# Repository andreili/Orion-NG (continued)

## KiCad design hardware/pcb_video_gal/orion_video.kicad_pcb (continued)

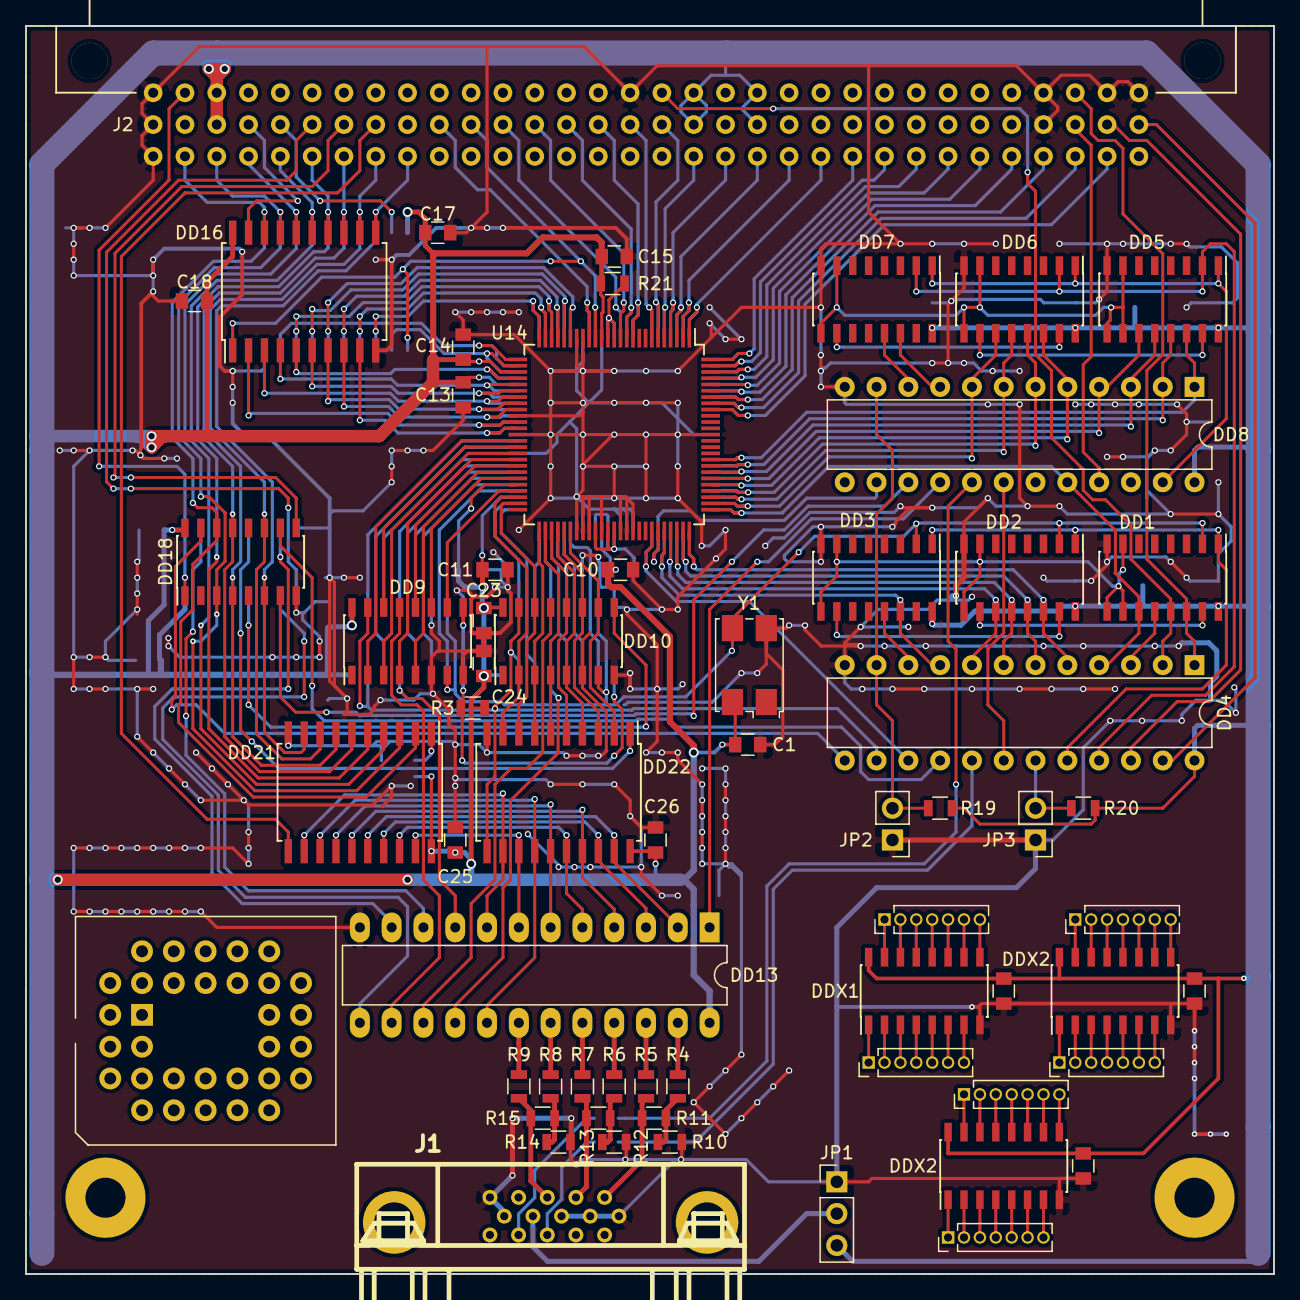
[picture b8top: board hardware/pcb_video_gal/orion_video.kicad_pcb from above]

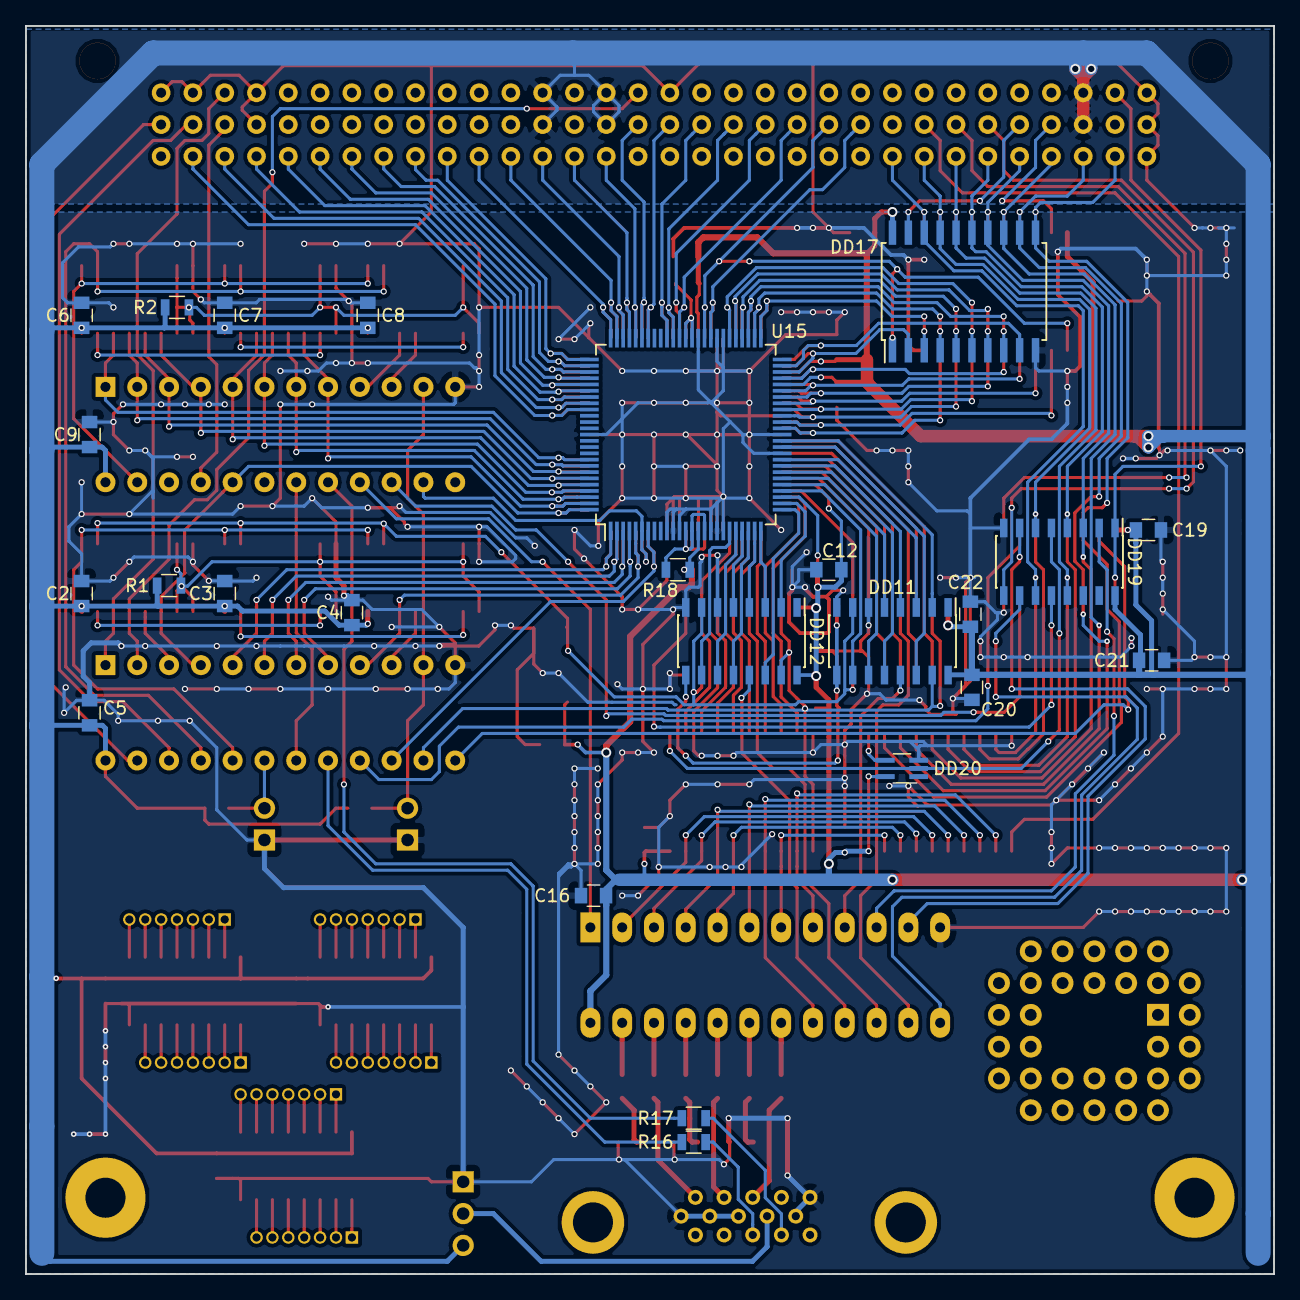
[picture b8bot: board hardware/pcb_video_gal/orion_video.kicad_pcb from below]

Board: 2 copper layers, 99.7 x 99.7 mm, 87 parts (25 on the bottom side), 181 nets.

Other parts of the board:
C27#2, C27#3: 100n; C_0805
DDX1, DDX2, DDX2#2: KP11; SOIC-16_3.9x9.9mm_Pitch1.27mm
J3#2, J3#3, J4#2, J4#3: RES1; Pin_Header_Straight_1x07_Pitch1.27mm

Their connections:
GND: C27#2.2, C27#3.2, DDX1.8, DDX2.8, DDX2#2.8; also elsewhere on the board
R1: DDX1.1, DDX2.1, DDX2#2.1, J3#2.1, J3#3.1; also elsewhere on the board
R2: DDX1.2, DDX2.2, DDX2#2.2, J3#2.2, J3#3.2; also elsewhere on the board
R3: DDX1.3, DDX2.3, DDX2#2.3, J3#2.3, J3#3.3; also elsewhere on the board
R4: DDX1.4, DDX2.4, DDX2#2.4, J3#2.4, J3#3.4; also elsewhere on the board
R5: DDX1.5, DDX2.5, DDX2#2.5, J3#2.5, J3#3.5; also elsewhere on the board
R6: DDX1.6, DDX2.6, DDX2#2.6, J3#2.6, J3#3.6; also elsewhere on the board
R7: DDX1.7, DDX2.7, DDX2#2.7, J3#2.7, J3#3.7; also elsewhere on the board
R9: DDX1.9, DDX2.9, DDX2#2.9, J4#2.7, J4#3.7; also elsewhere on the board
R10: DDX1.10, DDX2.10, DDX2#2.10, J4#2.6, J4#3.6; also elsewhere on the board
R11: DDX1.11, DDX2.11, DDX2#2.11, J4#2.5, J4#3.5; also elsewhere on the board
R12: DDX1.12, DDX2.12, DDX2#2.12, J4#2.4, J4#3.4; also elsewhere on the board
R13: DDX1.13, DDX2.13, DDX2#2.13, J4#2.3, J4#3.3; also elsewhere on the board
R14: DDX1.14, DDX2.14, DDX2#2.14, J4#2.2, J4#3.2; also elsewhere on the board
R15: DDX1.15, DDX2.15, DDX2#2.15, J4#2.1, J4#3.1; also elsewhere on the board
VCC: C27#2.1, C27#3.1, DDX1.16, DDX2.16, DDX2#2.16; also elsewhere on the board

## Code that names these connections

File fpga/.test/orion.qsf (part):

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set_location_assignment PIN_AJ24 -to ZD[2]
set_location_assignment PIN_AK24 -to ZD[1]
set_location_assignment PIN_AG23 -to ZD[0]
set_location_assignment PIN_AK23 -to ZRES
set_location_assignment PIN_AH23 -to ZCLK
set_location_assignment PIN_AK22 -to ZRFSH
set_location_assignment PIN_AJ22 -to ZINT
set_location_assignment PIN_AH22 -to ZMREQ
set_location_assignment PIN_AF24 -to ZIORQ
set_location_assignment PIN_AF23 -to ZWR
set_location_assignment PIN_AD21 -to ZRD
set_location_assignment PIN_AG22 -to ZM1
set_instance_assignment -name IO_STANDARD "3.3-V LVCMOS" -to ZA[1]
set_instance_assignment -name IO_STANDARD "3.3-V LVCMOS" -to ZA[0]
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
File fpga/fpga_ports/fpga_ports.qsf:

# -------------------------------------------------------------------------- #
#
# Copyright (C) 1991-2013 Altera Corporation
# Your use of Altera Corporation's design tools, logic functions 
# and other software and tools, and its AMPP partner logic 
# functions, and any output files from any of the foregoing 
# (including device programming or simulation files), and any 
# associated documentation or information are expressly subject 
# to the terms and conditions of the Altera Program License 
# Subscription Agreement, Altera MegaCore Function License 
# Agreement, or other applicable license agreement, including, 
# without limitation, that your use is for the sole purpose of 
# programming logic devices manufactured by Altera and sold by 
# Altera or its authorized distributors.  Please refer to the 
# applicable agreement for further details.
#
# -------------------------------------------------------------------------- #
#
# Quartus II 64-Bit
# Version 13.0.1 Build 232 06/12/2013 Service Pack 1 SJ Web Edition
# Date created = 19:53:07  June 26, 2018
#
# -------------------------------------------------------------------------- #
#
# Notes:
#
# 1) The default values for assignments are stored in the file:
#		fpga_vmem_assignment_defaults.qdf
#    If this file doesn't exist, see file:
#		assignment_defaults.qdf
#
# 2) Altera recommends that you do not modify this file. This
#    file is updated automatically by the Quartus II software
#    and any changes you make may be lost or overwritten.
#
# -------------------------------------------------------------------------- #


set_global_assignment -name FAMILY MAX7000S
set_global_assignment -name DEVICE "EPM7128STC100-7"
set_global_assignment -name TOP_LEVEL_ENTITY cpu_ports
set_global_assignment -name ORIGINAL_QUARTUS_VERSION "13.0 SP1"
set_global_assignment -name PROJECT_CREATION_TIME_DATE "19:53:07  JUNE 26, 2018"
set_global_assignment -name LAST_QUARTUS_VERSION "13.0 SP1"
set_global_assignment -name PROJECT_OUTPUT_DIRECTORY output_files
set_global_assignment -name DEVICE_FILTER_PACKAGE TQFP
set_global_assignment -name DEVICE_FILTER_PIN_COUNT 100
set_global_assignment -name DEVICE_FILTER_SPEED_GRADE 7
set_global_assignment -name ERROR_CHECK_FREQUENCY_DIVISOR "-1"

set_global_assignment -name MAX7000_DEVICE_IO_STANDARD TTL
set_location_assignment PIN_4 -to TDI
set_location_assignment PIN_15 -to TMS
set_location_assignment PIN_62 -to TCK
set_location_assignment PIN_73 -to TDO
set_location_assignment PIN_87 -to clk
set_global_assignment -name MAX7000_OPTIMIZATION_TECHNIQUE AREA
set_global_assignment -name SYNTH_TIMING_DRIVEN_SYNTHESIS OFF
set_global_assignment -name OPTIMIZE_HOLD_TIMING OFF
set_global_assignment -name OPTIMIZE_MULTI_CORNER_TIMING ON
set_global_assignment -name FITTER_EFFORT "STANDARD FIT"
set_location_assignment PIN_54 -to addr[0]
set_location_assignment PIN_24 -to addr[1]
set_location_assignment PIN_20 -to addr[2]
set_location_assignment PIN_97 -to addr[3]
set_location_assignment PIN_32 -to addr[4]
set_location_assignment PIN_28 -to addr[5]
set_location_assignment PIN_65 -to addr[6]
set_location_assignment PIN_98 -to addr[15]
set_location_assignment PIN_27 -to addr[7]
set_location_assignment PIN_85 -to addr[14]
set_location_assignment PIN_81 -to addr[8]
set_location_assignment PIN_94 -to addr[13]
set_location_assignment PIN_68 -to addr[9]
set_location_assignment PIN_30 -to addr[12]
set_location_assignment PIN_69 -to addr[10]
set_location_assignment PIN_56 -to addr[11]
set_global_assignment -name PRE_MAPPING_RESYNTHESIS OFF
set_global_assignment -name MAX7000_FANIN_PER_CELL 80
set_global_assignment -name IGNORE_CARRY_BUFFERS OFF
set_global_assignment -name IGNORE_CASCADE_BUFFERS OFF
set_global_assignment -name IGNORE_GLOBAL_BUFFERS OFF
set_global_assignment -name IGNORE_ROW_GLOBAL_BUFFERS OFF
set_global_assignment -name MAX7000_IGNORE_LCELL_BUFFERS AUTO
set_global_assignment -name MAX7000_IGNORE_SOFT_BUFFERS OFF
set_global_assignment -name AUTO_RESOURCE_SHARING OFF
set_global_assignment -name ECO_REGENERATE_REPORT OFF
set_global_assignment -name OPTIMIZE_IOC_REGISTER_PLACEMENT_FOR_TIMING "PACK ALL IO REGISTERS"
set_global_assignment -name FORCE_FITTER_TO_AVOID_PERIPHERY_PLACEMENT_WARNINGS OFF
set_global_assignment -name ALM_REGISTER_PACKING_EFFORT HIGH
set_global_assignment -name STATE_MACHINE_PROCESSING "MINIMAL BITS"
set_global_assignment -name VHDL_INPUT_VERSION VHDL_2008
set_global_assignment -name VHDL_SHOW_LMF_MAPPING_MESSAGES OFF
set_global_assignment -name AUTO_PARALLEL_EXPANDERS OFF

set_global_assignment -name AUTO_LCELL_INSERTION ON
set_global_assignment -name REMOVE_DUPLICATE_REGISTERS OFF
set_global_assignment -name SYNTHESIS_SEED 47
set_global_assignment -name AUTO_TURBO_BIT ON
set_global_assignment -name ECO_OPTIMIZE_TIMING ON
set_instance_assignment -name GLOBAL_SIGNAL "GLOBAL CLOCK" -to clk
set_location_assignment PIN_67 -to data[4]
set_location_assignment PIN_80 -to data[3]
set_location_assignment PIN_55 -to data[5]
set_global_assignment -name ASSIGNMENT_GROUP_MEMBER config -section_id config_gr
set_location_assignment PIN_22 -to rfshn
set_location_assignment PIN_92 -to m1n
set_location_assignment PIN_89 -to resetn
set_location_assignment PIN_58 -to waitn
set_location_assignment PIN_90 -to wrn
set_location_assignment PIN_33 -to rdn
set_location_assignment PIN_61 -to data[6]
set_location_assignment PIN_8 -to data[2]
set_location_assignment PIN_64 -to data[7]
set_location_assignment PIN_25 -to data[0]
set_location_assignment PIN_29 -to data[1]
set_location_assignment PIN_10 -to ram_vm_oe0
set_location_assignment PIN_9 -to ram_vm_oe1
set_location_assignment PIN_96 -to snd
set_location_assignment PIN_50 -to rom3_sel
set_location_assignment PIN_49 -to rom2_sel
set_location_assignment PIN_44 -to rom2_addr[13]
set_location_assignment PIN_45 -to rom2_addr[14]
set_location_assignment PIN_47 -to rom2_addr[15]
set_location_assignment PIN_48 -to rom2_addr[16]
set_location_assignment PIN_46 -to rom2_addr[17]
set_location_assignment PIN_52 -to rom2_addr[18]
set_location_assignment PIN_42 -to rom1_sel
set_location_assignment PIN_41 -to ram_wrn
set_location_assignment PIN_40 -to ram_rdn
set_location_assignment PIN_1 -to ram_cen_v
set_location_assignment PIN_14 -to ram_cen[0]
set_location_assignment PIN_16 -to ram_cen[1]
set_location_assignment PIN_17 -to ram_cen[2]
set_location_assignment PIN_19 -to ram_cen[3]
set_location_assignment PIN_99 -to pFC
set_location_assignment PIN_63 -to pFB
set_location_assignment PIN_100 -to pFA
set_location_assignment PIN_36 -to pF8
set_location_assignment PIN_93 -to mreqn
set_location_assignment PIN_23 -to MA[14]
set_location_assignment PIN_2 -to MA[15]
set_location_assignment PIN_7 -to MA[16]
set_location_assignment PIN_6 -to MA[17]
set_location_assignment PIN_5 -to MA[18]
set_location_assignment PIN_53 -to irq0n
set_location_assignment PIN_88 -to iorqn
set_location_assignment PIN_37 -to int50
set_location_assignment PIN_70 -to config[0]
set_location_assignment PIN_71 -to config[1]
set_location_assignment PIN_72 -to config[2]
set_location_assignment PIN_75 -to config[3]
set_location_assignment PIN_76 -to config[4]
set_location_assignment PIN_77 -to config[5]
set_location_assignment PIN_78 -to config[6]
set_location_assignment PIN_79 -to config[7]
set_location_assignment PIN_57 -to blion
set_location_assignment PIN_21 -to addr_hi[14]
set_location_assignment PIN_35 -to addr_hi[15]
set_location_assignment PIN_84 -to zclk
set_location_assignment PIN_60 -to clk_sel
set_location_assignment PIN_31 -to ram_16bit
set_location_assignment PIN_12 -to ram_buf_oe[0]
set_location_assignment PIN_13 -to ram_buf_oe[1]
set_location_assignment PIN_83 -to res
set_global_assignment -name SDC_FILE fpga_ports.out.sdc
set_global_assignment -name VHDL_FILE rtl/cpu_ports.vhd
set_global_assignment -name SEARCH_PATH rtl/ -tag from_archive

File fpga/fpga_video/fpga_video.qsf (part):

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set_instance_assignment -name IO_STANDARD "3.3-V LVCMOS" -to EXT3[5]
set_instance_assignment -name IO_STANDARD "3.3-V LVCMOS" -to EXT3[6]
set_instance_assignment -name IO_STANDARD "3.3-V LVCMOS" -to EXT3[7]
set_location_assignment PIN_K16 -to EXT1[5]
set_location_assignment PIN_J12 -to EXT1[4]
set_location_assignment PIN_J13 -to EXT1[3]
set_location_assignment PIN_J16 -to EXT1[2]
set_location_assignment PIN_J15 -to EXT1[1]
set_location_assignment PIN_J14 -to EXT1[0]
set_location_assignment PIN_B12 -to EXT0[7]
set_location_assignment PIN_B16 -to EXT0[6]
set_location_assignment PIN_D12 -to EXT0[5]
set_location_assignment PIN_A15 -to EXT0[4]
set_location_assignment PIN_A13 -to EXT0[3]
set_location_assignment PIN_A14 -to EXT0[2]
set_location_assignment PIN_B13 -to EXT0[1]
set_location_assignment PIN_B14 -to EXT0[0]
set_global_assignment -name ENABLE_SIGNALTAP ON
set_global_assignment -name USE_SIGNALTAP_FILE stp1.stp
set_location_assignment PIN_N9 -to EXT2_4
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set_location_assignment PIN_C11 -to IO1_14
set_location_assignment PIN_R11 -to EXT2_2
set_location_assignment PIN_R12 -to EXT2_1
set_location_assignment PIN_P9 -to EXT3[7]
set_location_assignment PIN_R9 -to EXT3[5]
set_location_assignment PIN_N5 -to EXT3[6]
set_location_assignment PIN_R6 -to EXT3[4]
set_location_assignment PIN_P8 -to EXT3[3]
set_location_assignment PIN_R7 -to EXT3[2]
set_instance_assignment -name IO_STANDARD "3.3-V LVCMOS" -to RESET_N
set_location_assignment PIN_P11 -to RESET_N
set_global_assignment -name OPTIMIZATION_MODE "AGGRESSIVE PERFORMANCE"
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
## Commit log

2018-05-07 Оптимизирована логика видеовыхода
2018-05-09 Оптимизация GAL_X - освобождён 1 выход для дальнейшего использования в менеджере памяти.
2018-05-10 Оптимизация прошавки GAL_X - добавлено формирование сигналов арбитража памяти и банков видеопамяти.
2018-05-11 Прошивки GAL обновлены до актуальных версий
2018-05-11 Завершена черновая схема видеомодуля.
2018-05-11 Обновлена схема видеомодуля
2018-05-11 Предварительное размещение элементов
2018-05-12 Исправления по схеме видеомодуля:
    1) Заменён системный разъём на DIN 41612;
    2) ПЗУ знакогенератора заменена на 28C512;
    3) Добавлена коммутация подачи питания на пин 9 разъёма VGA.
2018-05-15 Исправлен системный разъём - выполнен 3-х рядным DIN
2018-05-16 Обновлено расположение компонентов, разъём SYSTEM заменён на 3-х рядный.
2018-07-19 Добавлена реализация основных алгоритмов на CPLD
2018-07-19 Ширина андресной шины увеличена до 21 бита
2018-07-19 Добавлен проект FPGA для симуляции схемы
2018-07-31 Добавлен исходный код теста видеовывода
2018-08-21 Итоговая версия видеомодуля с использованием GAL.
    Включает в себя 256Кб памяти - используется двухпортовая для упрощения арбитража.
2018-08-21 Обновлены библиотеки KiCAD
2018-08-21 Тестовый проект FPGA обновлён до актуальной версии
2018-08-22 Актуализированы и протестированы прошивки для GAL видеомодуля.
    Тестировалось в FPGA-симуляции.
2018-08-27 Актуализирован проект FPGA
2018-08-27 Актуализированы прошивки GAL видеомодуля.
2018-08-27 Актуализированы схемы модулей видео и кросс-платы.
2018-08-27 Предварительная версия процессорного модуля
2018-09-02 Актуализация симуляции FPGA
2018-09-02 Обновлён проект платы процессорного модуля
2018-09-02 Управление УВВ вынесено в отдельный проект
2018-09-02 Добавлен исходный код модуля УВВ
2018-09-04 Дополнено взаимодейтсвие с STM32
2018-09-04 Исправлено тактирование CPU
2018-09-15 Исправлено ядро T80
2018-09-15 Обновлены используемые ROM
2018-09-15 Исправлена опечатка выборки второго банка видеопамяти
2018-09-15 Актуализирована обработка порта клавиатуры
2018-09-23 GAL X: иправлены опечатки
2018-10-04 RC версия процессорного модуля
2018-10-04 Обновлена прошивка CPLD процессорного модуля
2018-10-04 Исправлена обработка ROM-диска
2018-10-28 Обновлена прошивка для процессорного модуля и добавлен схемный вариант.
2018-10-28 Обновлена плата процессорного модуля - версия для производства.
2018-10-28 Добавлены схема и плата модуля для подключения к DE1-SoC
2021-03-14 Актуализированна аппаратная часть
2021-03-14 Добавлена прошивка видео-модуля
2021-03-14 Обновлены исключения
2021-03-14 Обновлён тест
2021-03-14 Удалены лишние файлы
2021-03-14 Обновлены прошивки GAL
2021-04-03 Обновлено до последней версии HW.
2021-04-23 Добавлена проверка наличия FPGA. Исправлена работа UART.
2021-06-26 Удалены неиспользуемы аппаратные модули.
2021-06-26 Исправлено предупреждение компилятора
2021-08-06 Черновик видео-контроллера.
2021-08-06 Обновлена прошивка видео-контроллера.
2021-08-21 * Стабилизирована работа SDRAM. * Функционал разнесён по модулям. * Упрощённая версия захвата записи в память, без поддержки переключения банков (только 64К).
2021-08-21 Исправлен размер посылки.
2021-08-21 Исправлен делитель SPI для большей стабильности.
2021-08-21 Оптимизация контроллера SDRAM.
2021-08-25 Тестовый проект с RISC-V ядром.
2021-10-14 Добавлена поддержка модуля видеозахвата.
2021-11-28 Add debug purpose for memory.
2021-11-28 Change I2C speed.
2021-11-28 Add delay function.
2021-11-28 Add base display driver.
2021-11-30 Re-organize structure for sources.
2021-12-01 Move hardware part to HIL driver
2021-12-02 Add DMA driver (for display transactions).
2021-12-02 Fix assert code
2021-12-02 Move graphical parts to GUI class.
